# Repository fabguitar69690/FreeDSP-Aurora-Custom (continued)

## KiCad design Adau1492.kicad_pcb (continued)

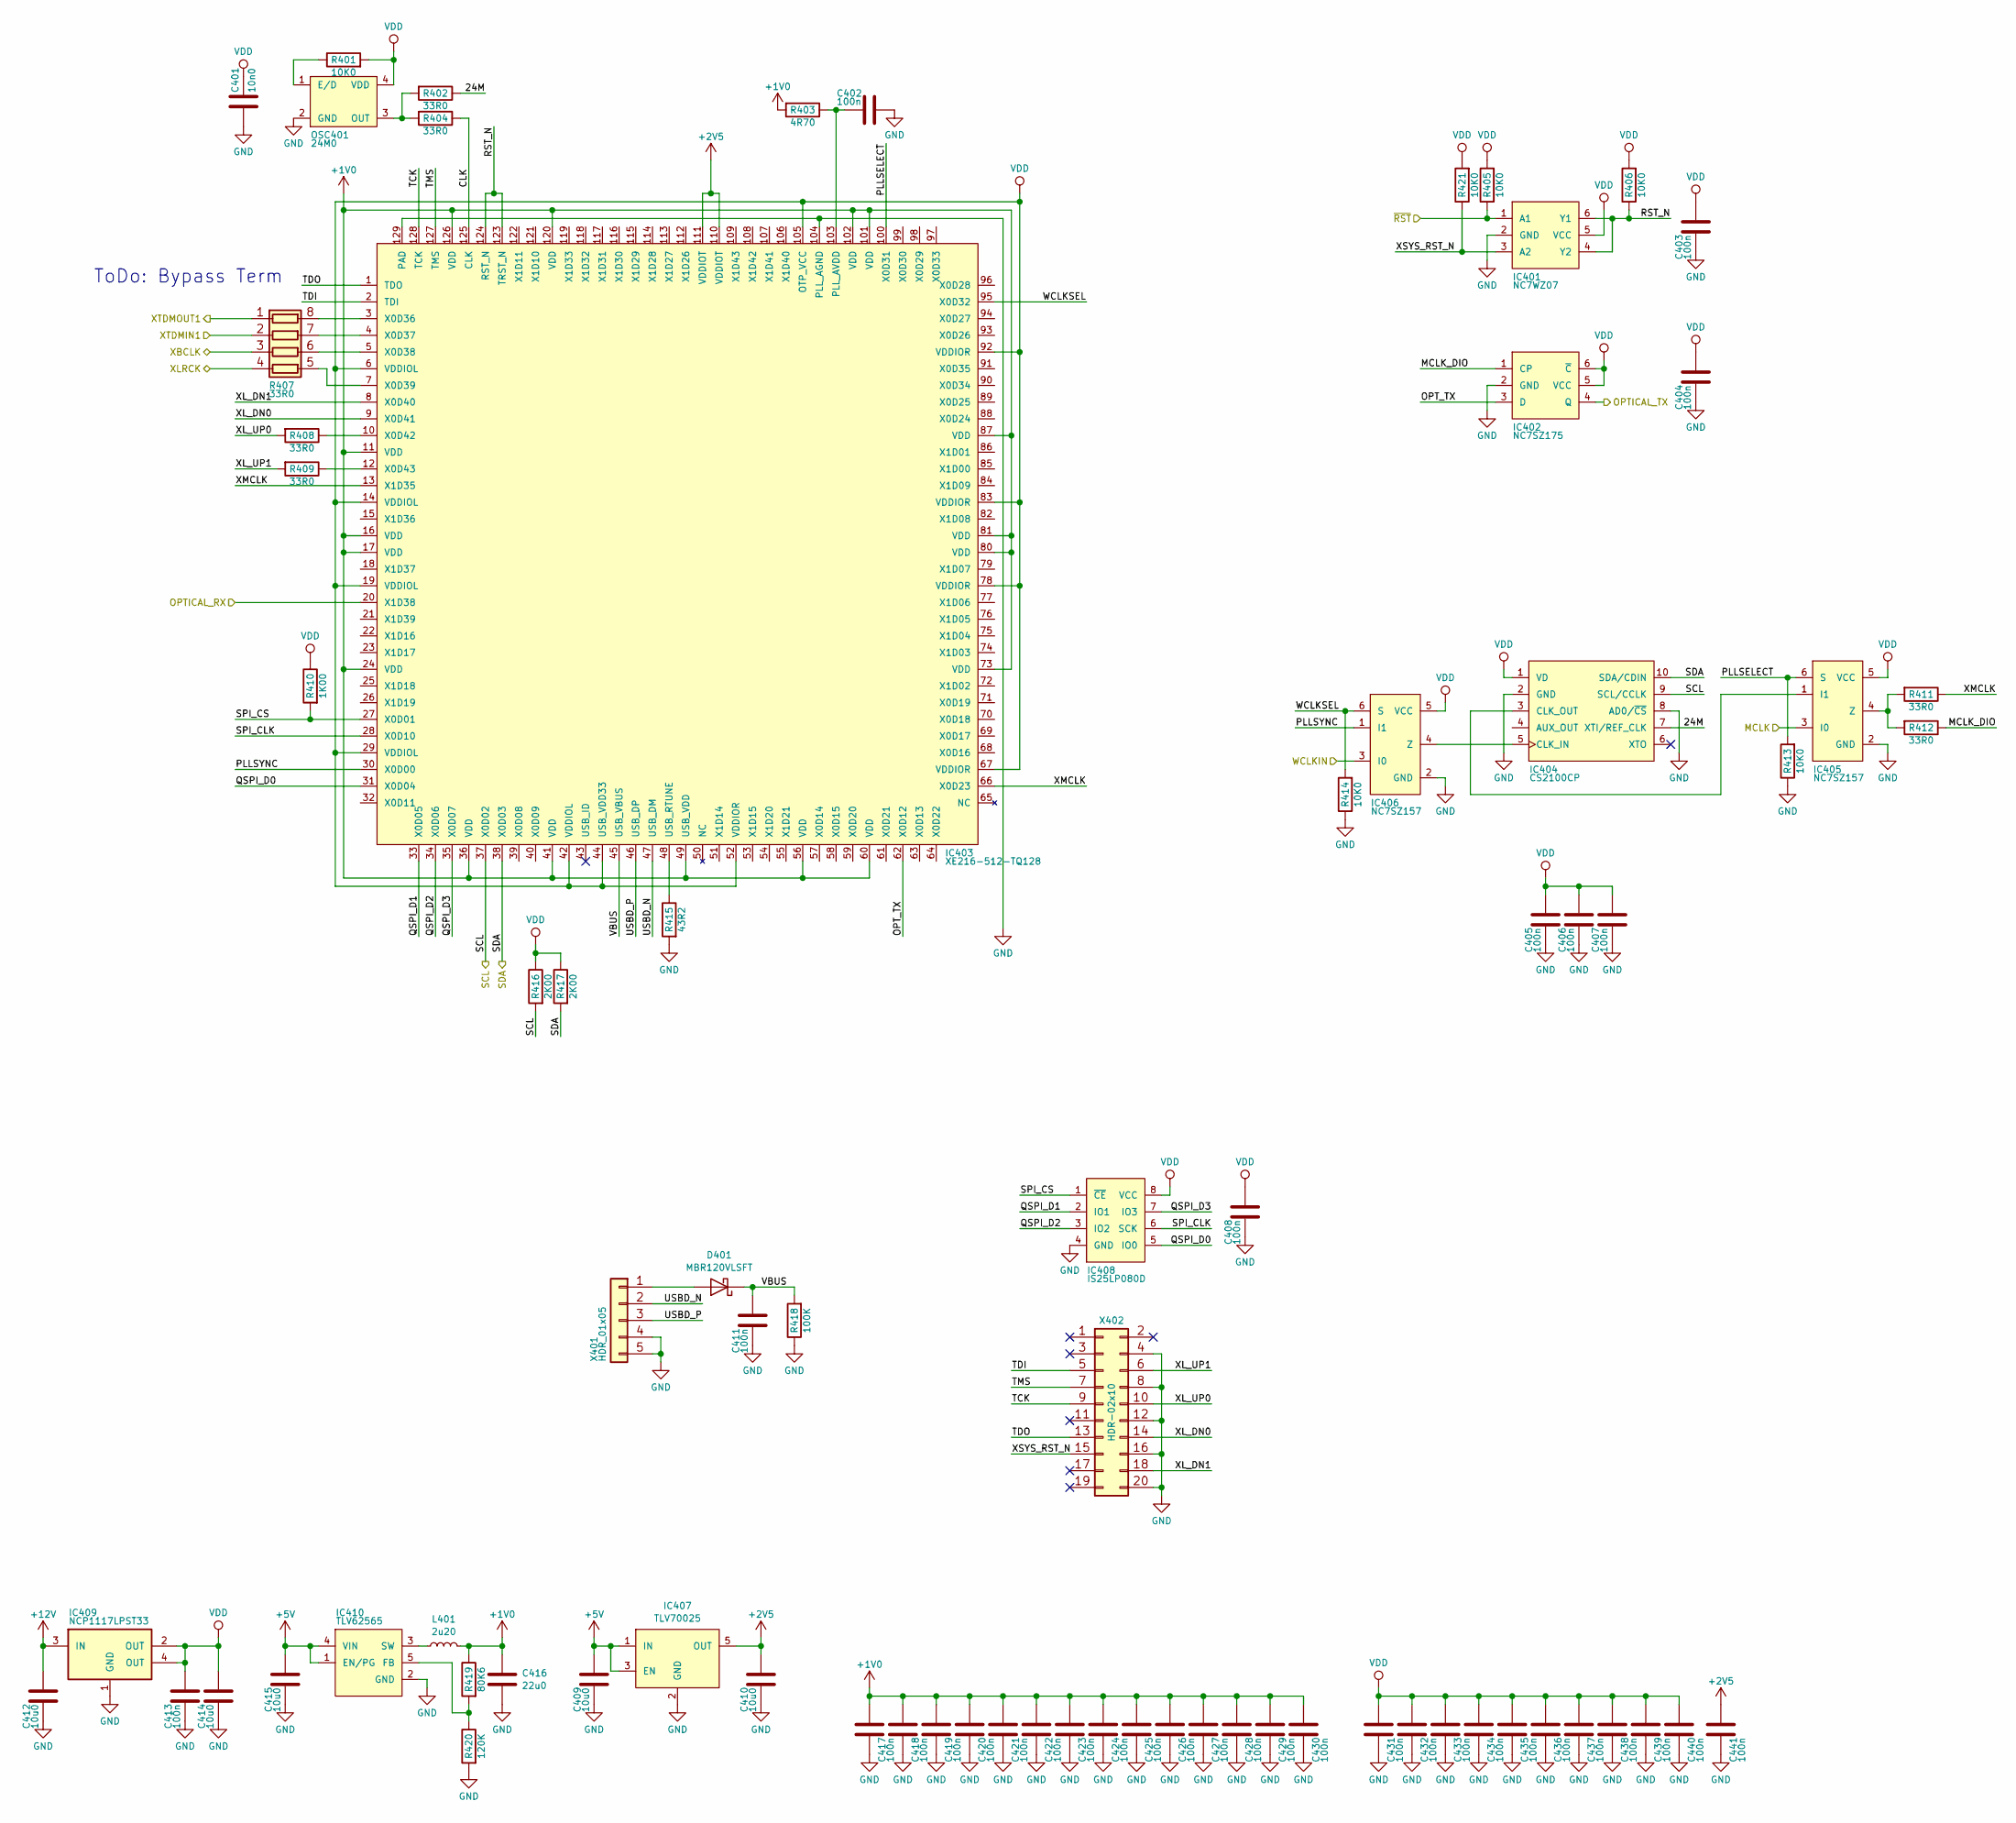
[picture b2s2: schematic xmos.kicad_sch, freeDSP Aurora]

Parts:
C401: CAP_10n0_50V_X7R_0805; C_0805_2012Metric_Pad1.18x1.45mm_HandSolder; digikey 311-1136-1-ND
C402, C403, C404, C405, C406, C407, C408, C411, C413: CAP_100n_50V_X7R_0805; C_0805_2012Metric_Pad1.18x1.45mm_HandSolder; digikey 399-1170-1-ND
C409, C410, C412, C414, C415: CAP_10u0_25V_X5R_0805; C_0805_2012Metric_Pad1.18x1.45mm_HandSolder; digikey 490-10748-1-ND
C416: CAP_22u0_10V_X5R_0805; C_0805_2012Metric_Pad1.18x1.45mm_HandSolder; digikey 490-10511-1-ND
C417, C418, C419, C420, C421, C422, C423, C424, C425, C426, C427, C428, C429, C430, C431, C432, C433, C434, C435, C436, C437, C438, C439, C440, C441: CAP_100n_10V_X7R_0402; C_0402; digikey 490-6321-1-ND
D401: DIO_MBR120VLSFT; D_SOD-123; digikey MBR120VLSFT3GOSCT-ND
IC401: IC_NC7WZ07; SC-70-6; digikey NC7WZ07P6XCT-ND
IC402: NC7SZ175; SOT-363_SC-70-6; digikey 296-16998-1-ND
IC403: IC_XE216-512-TQ128; QFP40P1600X1600X120-129N; digikey 880-1096-ND
IC404: IC_CS2100CP; MSOP-10_3x3mm_Pitch0.5mm; digikey 598-1750-ND
IC405, IC406: NC7SZ157; SC-70-6; digikey NC7SZ157P6XCT-ND
IC407: TLV70025; SOT-353_SC-70-5_Handsoldering; digikey 296-27793-1-ND
IC408: IC_IS25LP080D; SOIC-8_3.9x4.9mm_P1.27mm; digikey 706-1580-ND
IC409: IC_NCP1117LPST33; SOT-223; digikey NCP1117LPST33T3GOSCT-ND
IC410: IC_TLV62565; SOT-23-5_HandSoldering; digikey 296-43657-1-ND
L401: IND_2U20_30%_4A5; INDPM7073X355N; digikey 811-1157-1-ND
OSC401: OSC_24M0; ASFL120000MHZEKT; digikey 300-8252-1-ND
R401, R405, R406, R413, R414, R421: RES_10K0_1%_0.125W_Thick_0805; R_0805_2012Metric_Pad1.20x1.40mm_HandSolder; digikey 311-10.0KCRCT-ND
R402, R404, R408, R409, R411, R412: RES_33R0_1%_0.125W_Thick_0805; R_0805_2012Metric_Pad1.20x1.40mm_HandSolder; digikey 311-33.0CRCT-ND
R403: RES_4R70_1%_0.125W_Thick_0805; R_0805_2012Metric_Pad1.20x1.40mm_HandSolder; digikey 311-4.70CRCT-ND
R407: 33R0_5%_4x0603; R_Array_Convex_4x0603; digikey TC164J-33CT-ND
R410: RES_1K00_1%_0.125W_Thick_0805; R_0805_2012Metric_Pad1.20x1.40mm_HandSolder; digikey 311-1.00KCRCT-ND
R415: RES_43R2_1%_0.125W_Thick_0805; R_0805_2012Metric_Pad1.20x1.40mm_HandSolder; digikey P43.2CCT-ND
R416, R417: RES_2K00_1%_0.125W_Thick_0805; R_0805_2012Metric_Pad1.20x1.40mm_HandSolder; digikey 311-2.00KCRCT-ND
R418: RES_100K_1%_0.125W_Thick_0805; R_0805_2012Metric_Pad1.20x1.40mm_HandSolder; digikey 311-100KCRCT-ND
R419: RES_80K6_1%_0.125W_Thick_0805; R_0805_2012Metric_Pad1.20x1.40mm_HandSolder; digikey 311-80.6KCRCT-ND
R420: RES_120K_1%_0.125W_Thick_0805; R_0805_2012Metric_Pad1.20x1.40mm_HandSolder; digikey 311-120KCRCT-ND
X401: HDR_01x05; PinSocket_1x05_P2.54mm_Vertical; digikey S1011EC-05-ND
X402: CON_HDR_02x10; PinSocket_2x10_P2.54mm_Vertical; digikey S2011EC-10-ND

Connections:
+1V0: C416.1, C417.1, C418.1, C419.1, C420.1, C421.1, C422.1, C423.1, C424.1, C425.1, C426.1, C427.1, C428.1, C429.1, C430.1, IC403.11 (VDD), IC403.16 (VDD), IC403.17 (VDD), IC403.24 (VDD), IC403.36 (VDD), IC403.41 (VDD), IC403.49 (USB_VDD), IC403.56 (VDD), IC403.60 (VDD), IC403.73 (VDD), IC403.80 (VDD), IC403.81 (VDD), IC403.87 (VDD), IC403.101 (VDD), IC403.102 (VDD), IC403.120 (VDD), IC403.126 (VDD), L401.2, R403.2, R419.1
+2V5: C410.2, C441.1, IC403.110 (VDDIOT), IC403.111 (VDDIOT), IC407.5 (OUT)
+5V: C409.2, C415.2, IC407.1 (IN), IC407.3 (EN), IC410.1 (EN/PG), IC410.4 (VIN); also elsewhere on the board
+12V: C412.2, IC409.3 (IN); also elsewhere on the board
/MCLK: IC405.3 (I0); also elsewhere on the board
/OPTICAL_RX: IC403.20 (X1D38); also elsewhere on the board
/OPTICAL_TX: IC402.4 (Q); also elsewhere on the board
/WCLK_RX: IC406.3 (I0); also elsewhere on the board
/XMOS/24M: IC404.7 (XTI/REF_CLK), R402.1
/XMOS/CLK: IC403.125 (CLK), R404.1
/XMOS/MCLK_DIO: IC402.1 (CP), R412.1
/XMOS/OPT_TX: IC402.3 (D), IC403.62 (X0D12)
/XMOS/PLLSELECT: IC403.100 (X0D31), IC405.6 (S), R413.2
/XMOS/PLLSYNC: IC403.30 (X0D00), IC406.1 (I1)
/XMOS/QSPI_D0: IC403.31 (X0D04), IC408.5 (IO0)
/XMOS/QSPI_D1: IC403.33 (X0D05), IC408.2 (IO1)
/XMOS/QSPI_D2: IC403.34 (X0D06), IC408.3 (IO2)
/XMOS/QSPI_D3: IC403.35 (X0D07), IC408.7 (IO3)
/XMOS/RST_N: IC401.4 (Y2), IC401.6 (Y1), IC403.123 (TRST_N), IC403.124 (RST_N), R406.1
/XMOS/SPI_CLK: IC403.28 (X0D10), IC408.6 (SCK)
/XMOS/SPI_CS: IC403.27 (X0D01), IC408.1 (~CE), R410.2
/XMOS/TCK: IC403.128 (TCK), X402.9
/XMOS/TDI: IC403.2 (TDI), X402.5
/XMOS/TDO: IC403.1 (TDO), X402.13
/XMOS/TMS: IC403.127 (TMS), X402.7
/XMOS/USBD_N: IC403.47 (USB_DM), X401.2
/XMOS/USBD_P: IC403.46 (USB_DP), X401.3
/XMOS/VBUS: C411.2, D401.1 (K), IC403.45 (USB_VBUS), R418.2
/XMOS/WCLKSEL: IC403.95 (X0D32), IC406.6 (S), R414.2
/XMOS/XL_DN0: IC403.9 (X0D41), X402.14
/XMOS/XL_DN1: IC403.8 (X0D40), X402.18
/XMOS/XL_UP0: R408.2, X402.10
/XMOS/XL_UP1: R409.2, X402.6
/XMOS/XMCLK: IC403.13 (X1D35), IC403.66 (X0D23), R411.1
/XMOS/XSYS_RST_N: IC401.3 (A2), R421.1, X402.15
/xBCLK: R407.3 (R3.1); also elsewhere on the board
/xLRCK: R407.4 (R4.1); also elsewhere on the board
/xSCL: IC403.37 (X0D02), IC404.9 (SCL/CCLK), R416.2
/xSDA: IC403.38 (X0D03), IC404.10 (SDA/CDIN), R417.2
/xTDMIN: R407.2 (R2.1); also elsewhere on the board
/xTDMOUT: R407.1 (R1.1); also elsewhere on the board
/~RST: IC401.1 (A1), R405.1; also elsewhere on the board
GND: C401.1, C402.2, C403.1, C404.1, C405.1, C406.1, C407.1, C408.1, C409.1, C410.1, C411.1, C412.1, C413.1, C414.1, C415.1, C416.2, C417.2, C418.2, C419.2, C420.2, C421.2, C422.2, C423.2, C424.2, C425.2, C426.2, C427.2, C428.2, C429.2, C430.2, C431.2, C432.2, C433.2, C434.2, C435.2, C436.2, C437.2, C438.2, C439.2, C440.2, C441.2, IC401.2 (GND), IC402.2 (GND), IC403.104 (PLL_AGND), IC403.129 (PAD), IC404.2 (GND), IC404.8 (AD0/~CS), IC405.2 (GND), IC406.2 (GND), IC407.2 (GND), IC408.4 (GND), IC409.1 (GND), IC410.2 (GND), OSC401.2 (GND), R413.1, R414.1, R415.2, R418.1, R420.2, X401.4, X401.5, X402.4, X402.8, X402.12, X402.16, X402.20; also elsewhere on the board
unnamed: C402.1, IC403.103 (PLL_AVDD), R403.1
unnamed: D401.2 (A), X401.1
unnamed: IC403.3 (X0D36), R407.8 (R1.2)
unnamed: IC403.4 (X0D37), R407.7 (R2.2)
unnamed: IC403.5 (X0D38), R407.6 (R3.2)
unnamed: IC403.7 (X0D39), R407.5 (R4.2)
unnamed: IC403.10 (X0D42), R408.1
unnamed: IC403.12 (X0D43), R409.1
unnamed: IC403.48 (USB_RTUNE), R415.1
unnamed: IC404.3 (CLK_OUT), IC405.1 (I1)
unnamed: IC404.5 (CLK_IN), IC406.4 (Z)
unnamed: IC405.4 (Z), R411.2, R412.2
unnamed: IC410.3 (SW), L401.1
unnamed: IC410.5 (FB), R419.2, R420.1
unnamed: OSC401.1 (E/D), R401.1
unnamed: OSC401.3 (OUT), R402.2, R404.2
VDD: C401.2, C403.2, C404.2, C405.2, C406.2, C407.2, C408.2, C413.2, C414.2, C431.1, C432.1, C433.1, C434.1, C435.1, C436.1, C437.1, C438.1, C439.1, C440.1, IC401.5 (VCC), IC402.5 (VCC), IC402.6 (~C), IC403.6 (VDDIOL), IC403.14 (VDDIOL), IC403.19 (VDDIOL), IC403.29 (VDDIOL), IC403.42 (VDDIOL), IC403.44 (USB_VDD33), IC403.52 (VDDIOR), IC403.67 (VDDIOR), IC403.78 (VDDIOR), IC403.83 (VDDIOR), IC403.92 (VDDIOR), IC403.105 (OTP_VCC), IC404.1 (VD), IC405.5 (VCC), IC406.5 (VCC), IC408.8 (VCC), IC409.2 (OUT), IC409.4 (OUT), OSC401.4 (VDD), R401.2, R405.2, R406.2, R410.1, R416.1, R417.1, R421.2; also elsewhere on the board

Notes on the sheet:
ToDo: Bypass Term

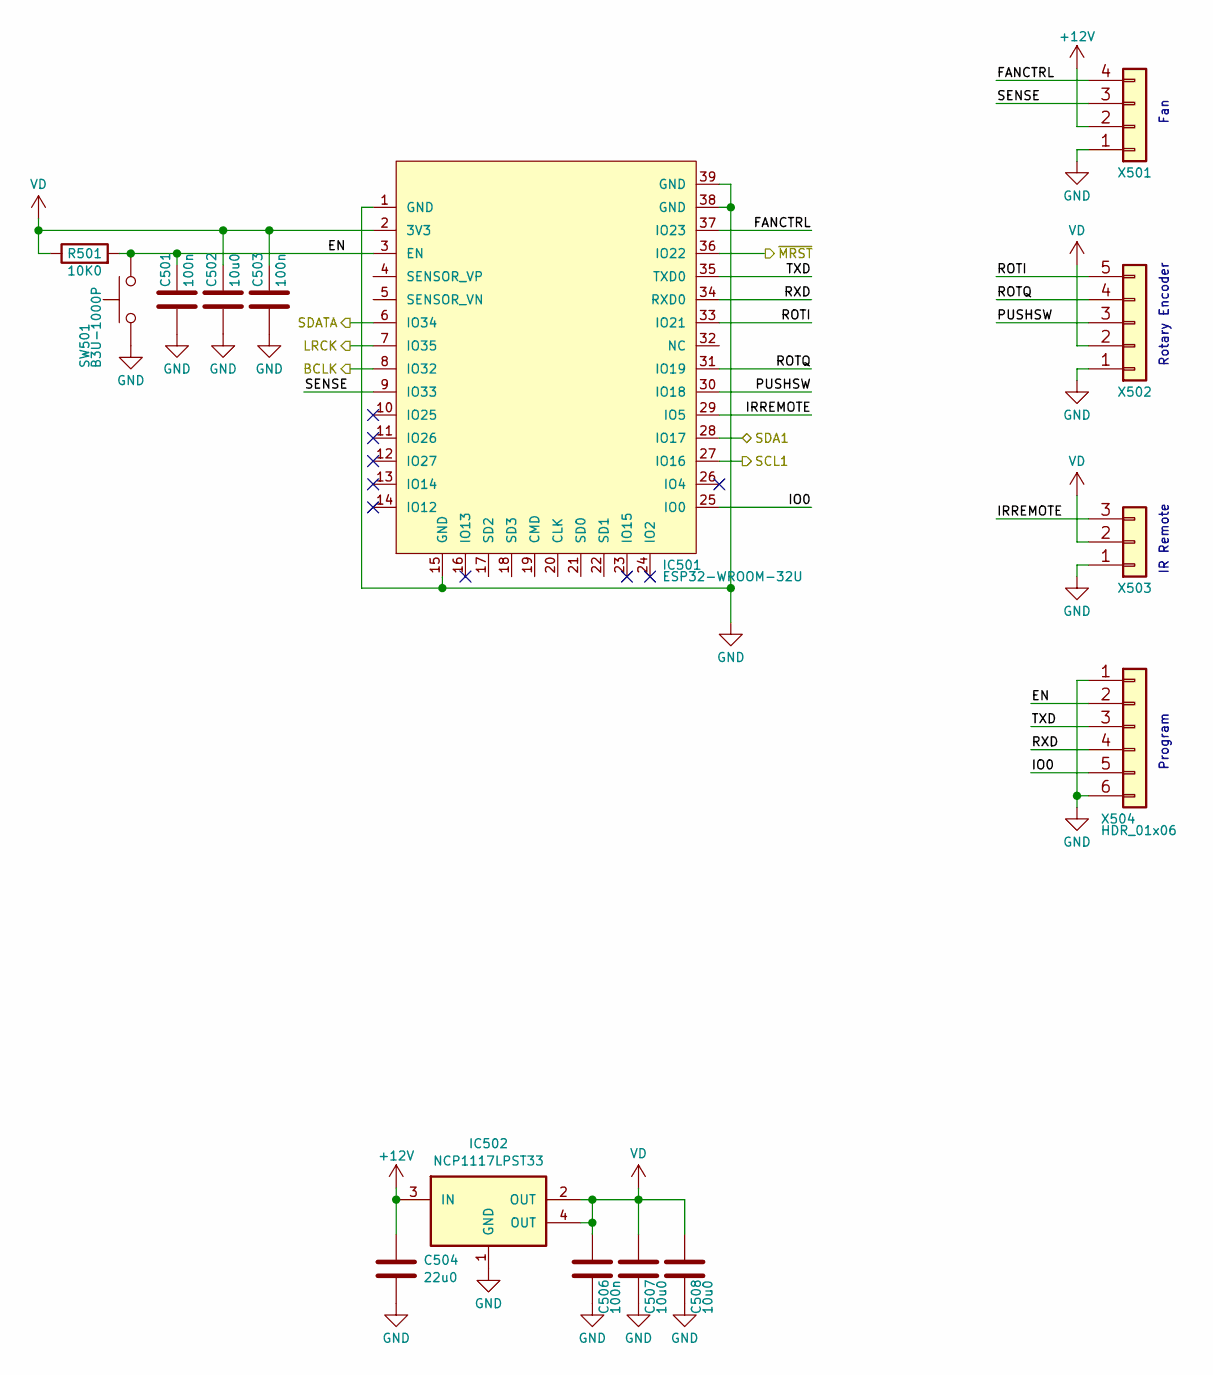
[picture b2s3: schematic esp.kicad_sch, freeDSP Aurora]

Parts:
C501, C503, C506: CAP_100n_50V_X7R_0805; C_0805_2012Metric_Pad1.18x1.45mm_HandSolder; digikey 399-1170-1-ND
C502, C507, C508: CAP_10u0_25V_X5R_0805; C_0805_2012Metric_Pad1.18x1.45mm_HandSolder; digikey 490-10748-1-ND
C504: CAP_22u0_10V_X5R_0805; C_0805_2012Metric_Pad1.18x1.45mm_HandSolder; digikey 490-10511-1-ND
IC501: ESP32-WROOM-32U; digikey 1904-1026-1-ND
IC502: IC_NCP1117LPST33; SOT-223; digikey NCP1117LPST33T3GOSCT-ND
R501: RES_10K0_1%_0.125W_Thick_0805; R_0805_2012Metric_Pad1.20x1.40mm_HandSolder; digikey 311-10.0KCRCT-ND
SW501: SW_Push; SW_SPST_B3U-1000P; digikey SW1020CT-ND
X501: Conn_01x04; PinSocket_1x04_P2.54mm_Vertical; digikey WM4202-ND
X502: Conn_01x05; PinSocket_1x05_P2.54mm_Vertical; digikey WM1734-ND
X503: Conn_01x03; PinSocket_1x03_P2.54mm_Vertical; digikey WM1732-ND
X504: HDR_01x06; PinHeader_1x06_P2.54mm_Vertical; digikey S1011EC-06-ND

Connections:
+12V: C504.1, IC502.3 (IN), X501.2; also elsewhere on the board
/BCLK:2: IC501.8 (IO32); also elsewhere on the board
/ESP32/EN: C501.2, IC501.3 (EN), R501.2, SW501.2, X504.2
/ESP32/FANCTRL: IC501.37 (IO23), X501.4
/ESP32/IO0: IC501.25 (IO0), X504.5
/ESP32/IRREMOTE: IC501.29 (IO5), X503.3
/ESP32/PUSHSW: IC501.30 (IO18), X502.3
/ESP32/ROTI: IC501.33 (IO21), X502.5
/ESP32/ROTQ: IC501.31 (IO19), X502.4
/ESP32/RXD: IC501.34 (RXD0), X504.4
/ESP32/SENSE: IC501.9 (IO33), X501.3
/ESP32/TXD: IC501.35 (TXD0), X504.3
/LRCK:2: IC501.7 (IO35); also elsewhere on the board
/MDI:2: IC501.6 (IO34); also elsewhere on the board
/SCL: IC501.27 (IO16); also elsewhere on the board
/SDA: IC501.28 (IO17); also elsewhere on the board
/~USBRST: IC501.36 (IO22); also elsewhere on the board
GND: C501.1, C502.1, C503.1, C504.2, C506.2, C507.2, C508.2, IC501.1 (GND), IC501.15 (GND), IC501.38 (GND), IC501.39 (GND), IC502.1 (GND), SW501.1, X501.1, X502.1, X503.1, X504.1, X504.6; also elsewhere on the board
VD: C502.2, C503.2, C506.1, C507.1, C508.1, IC501.2 (3V3), IC502.2 (OUT), IC502.4 (OUT), R501.1, X502.2, X503.2

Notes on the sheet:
Fan
Rotary Encoder
Program
IR Remote

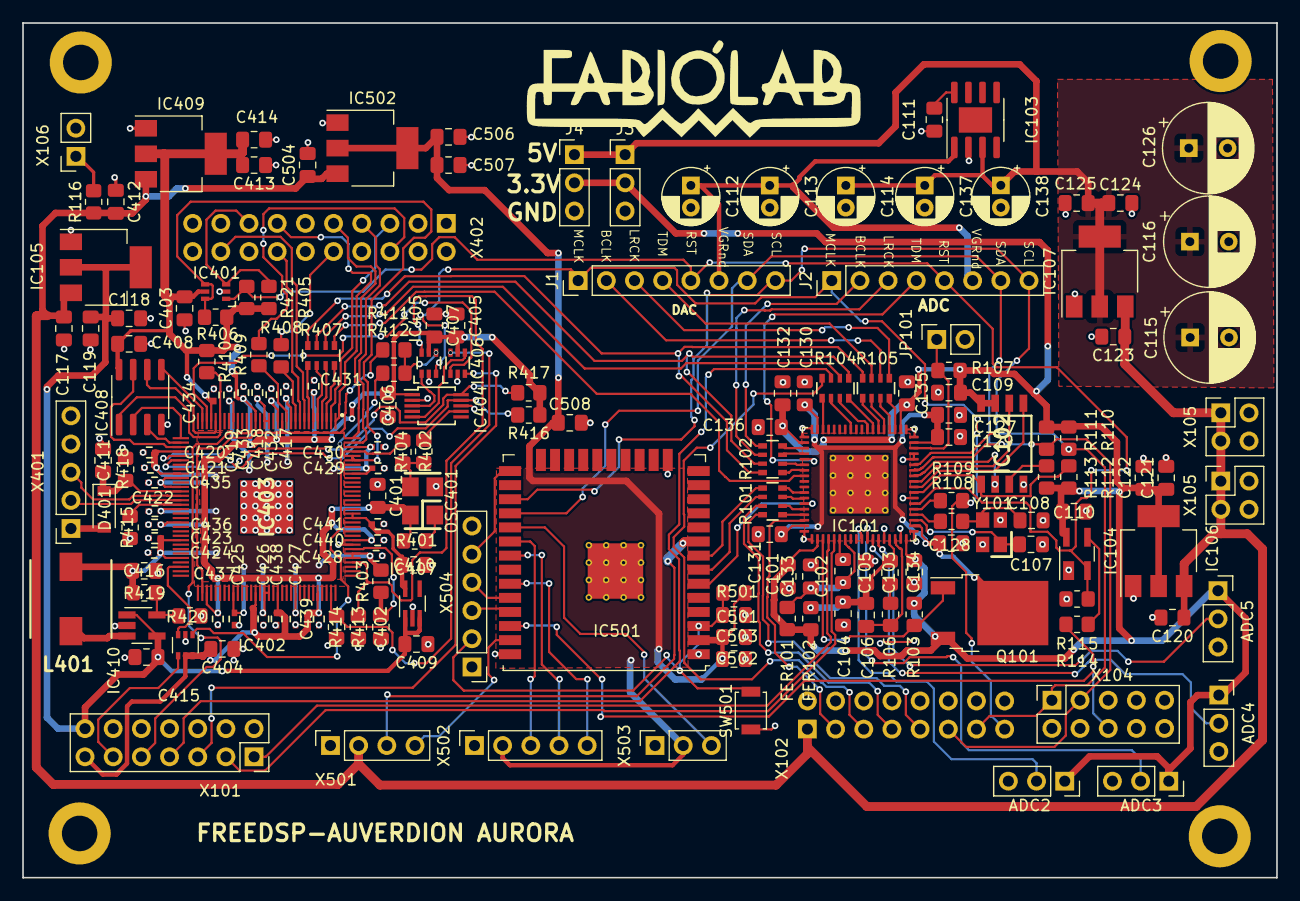
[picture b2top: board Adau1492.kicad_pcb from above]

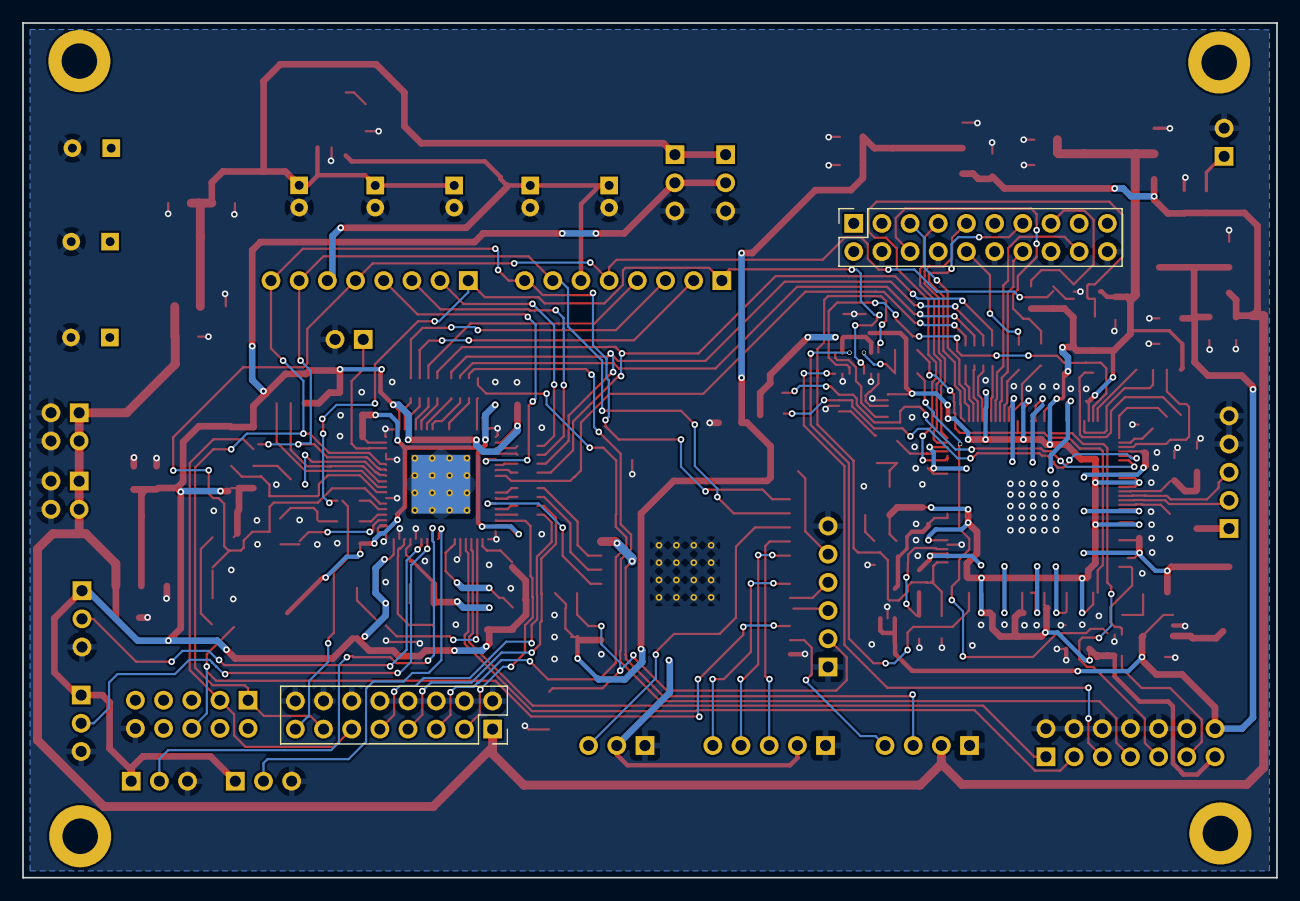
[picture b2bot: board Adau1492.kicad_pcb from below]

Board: 2 copper layers, 113.0 x 77.0 mm, 176 parts (2 on the bottom side), 132 nets.

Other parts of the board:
ADC2, ADC3, ADC4, ADC5: Conn_01x03; PinSocket_1x03_P2.54mm_Vertical
X105#2: CON_MicroFit3_02x02; PinSocket_2x02_P2.54mm_Vertical

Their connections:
+3V3: ADC2.1, ADC3.1, ADC4.1, ADC5.1; also elsewhere on the board
+12V: X105#2.1, X105#2.2; also elsewhere on the board
/AUXADC2: ADC2.2; also elsewhere on the board
/AUXADC3: ADC3.2; also elsewhere on the board
/AUXADC4: ADC4.2; also elsewhere on the board
/AUXADC5: ADC5.2; also elsewhere on the board
GND: ADC2.3, ADC3.3, ADC4.3, ADC5.3, X105#2.3, X105#2.4; also elsewhere on the board

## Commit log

2023-03-23 Kicad-Aurora-Custom
2023-03-23 dossier
2023-03-23 DA4458
2023-03-23 ADAU1452
    This reverts commit 7c940f1e25de9b09b55df499a087b432f9bcea52.
2023-04-20 Organize
